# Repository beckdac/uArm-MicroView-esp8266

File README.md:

uArm-MicroView-esp8266
======================

uArm control PCB with MicroView (Arduino w/ OLED) and esp8266 WiFi/UART bridge

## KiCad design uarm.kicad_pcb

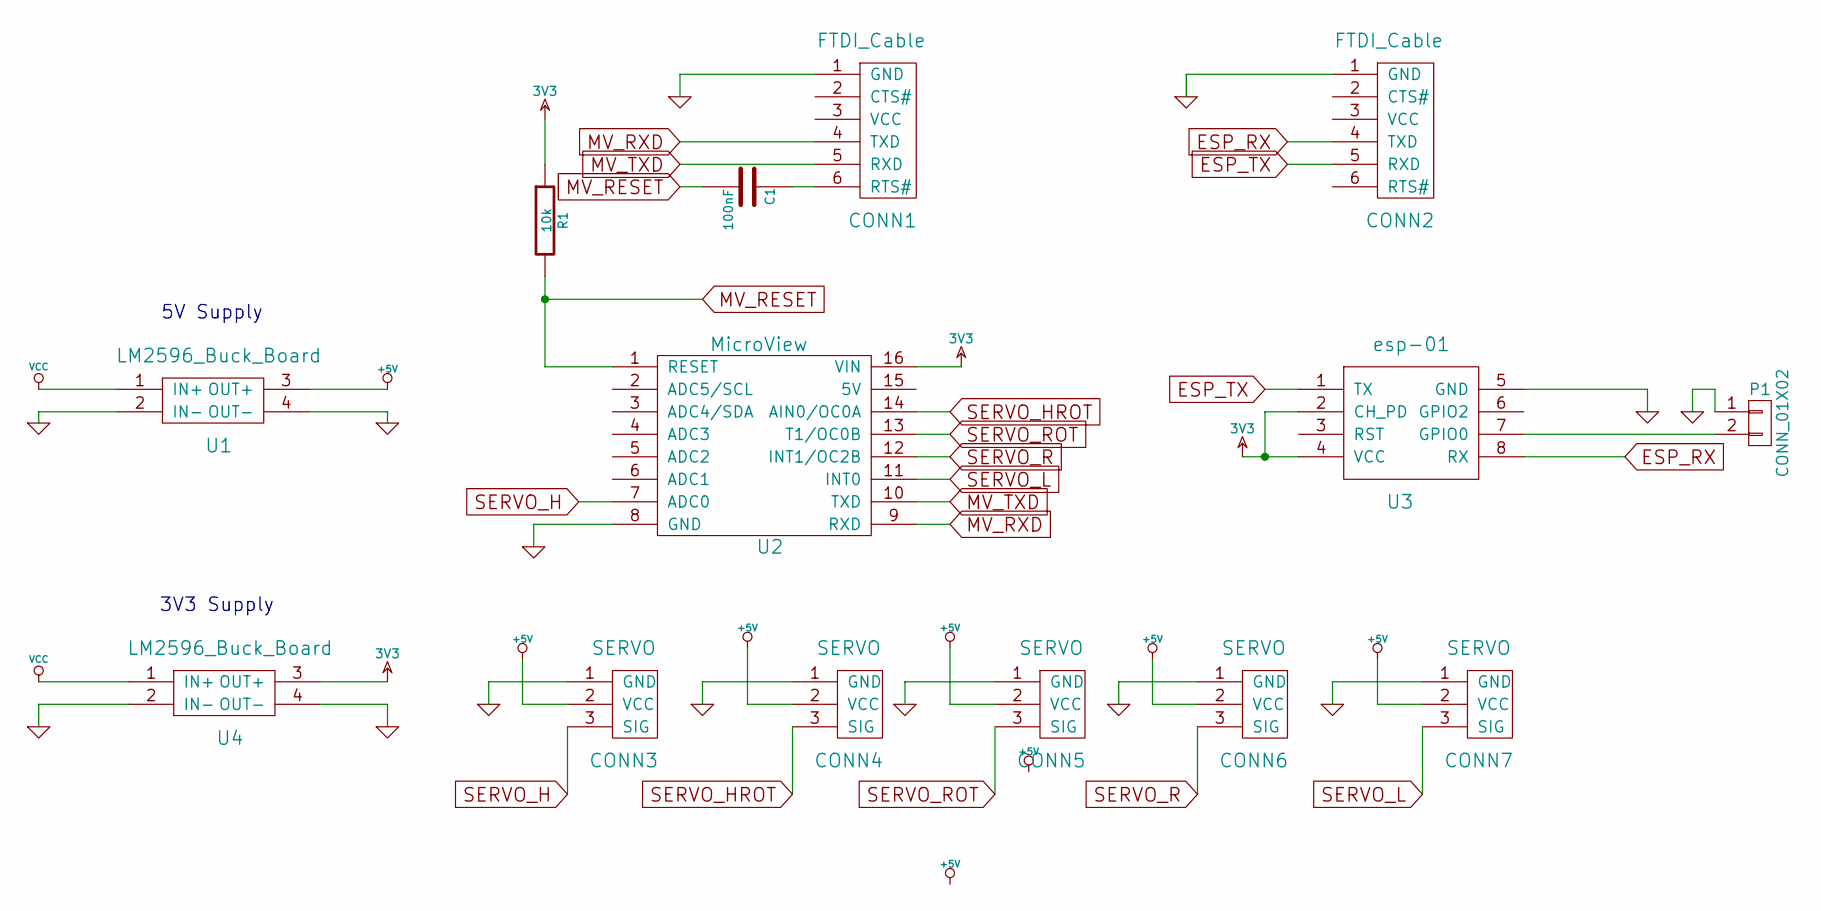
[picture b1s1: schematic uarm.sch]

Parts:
C1: 100nF; C1
CONN1, CONN2: FTDI_Cable; Pin_Header_Angled_1x06
CONN3, CONN4, CONN5, CONN6, CONN7: SERVO; Pin_Header_Straight_1x03
P1: CONN_01X02; Pin_Header_Straight_1x02
R1: 10k; R1
U1, U4: LM2596_Buck_Board; LM2596_BUCK_BOARD
U2: MicroView; MICROVIEW
U3: esp-01; ESP_01

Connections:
3V3: R1.1, U2.16 (VIN), U3.2 (CH_PD), U3.4 (VCC), U4.3 (OUT+)
+5V: CONN3.2 (VCC), CONN4.2 (VCC), CONN5.2 (VCC), CONN6.2 (VCC), CONN7.2 (VCC), U1.3 (OUT+)
ESP_RX: CONN2.4 (TXD), U3.8 (RX)
ESP_TX: CONN2.5 (RXD), U3.1 (TX)
GND: CONN1.1 (GND), CONN2.1 (GND), CONN3.1 (GND), CONN4.1 (GND), CONN5.1 (GND), CONN6.1 (GND), CONN7.1 (GND), P1.1, U1.2 (IN-), U1.4 (OUT-), U2.8 (GND), U3.5 (GND), U4.2 (IN-), U4.4 (OUT-)
MV_RESET: C1.2, R1.2, U2.1 (RESET)
MV_RXD: CONN1.4 (TXD), U2.9 (RXD)
MV_TXD: CONN1.5 (RXD), U2.10 (TXD)
unnamed: C1.1, CONN1.6 (RTS#)
unnamed: P1.2, U3.7 (GPIO0)
SERVO_H: CONN3.3 (SIG), U2.7 (ADC0)
SERVO_HROT: CONN4.3 (SIG), U2.14 (AIN0/OC0A)
SERVO_L: CONN7.3 (SIG), U2.11 (INT0)
SERVO_R: CONN6.3 (SIG), U2.12 (INT1/OC2B)
SERVO_ROT: CONN5.3 (SIG), U2.13 (T1/OC0B)
VCC: U1.1 (IN+), U4.1 (IN+)

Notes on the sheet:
5V Supply
3V3 Supply

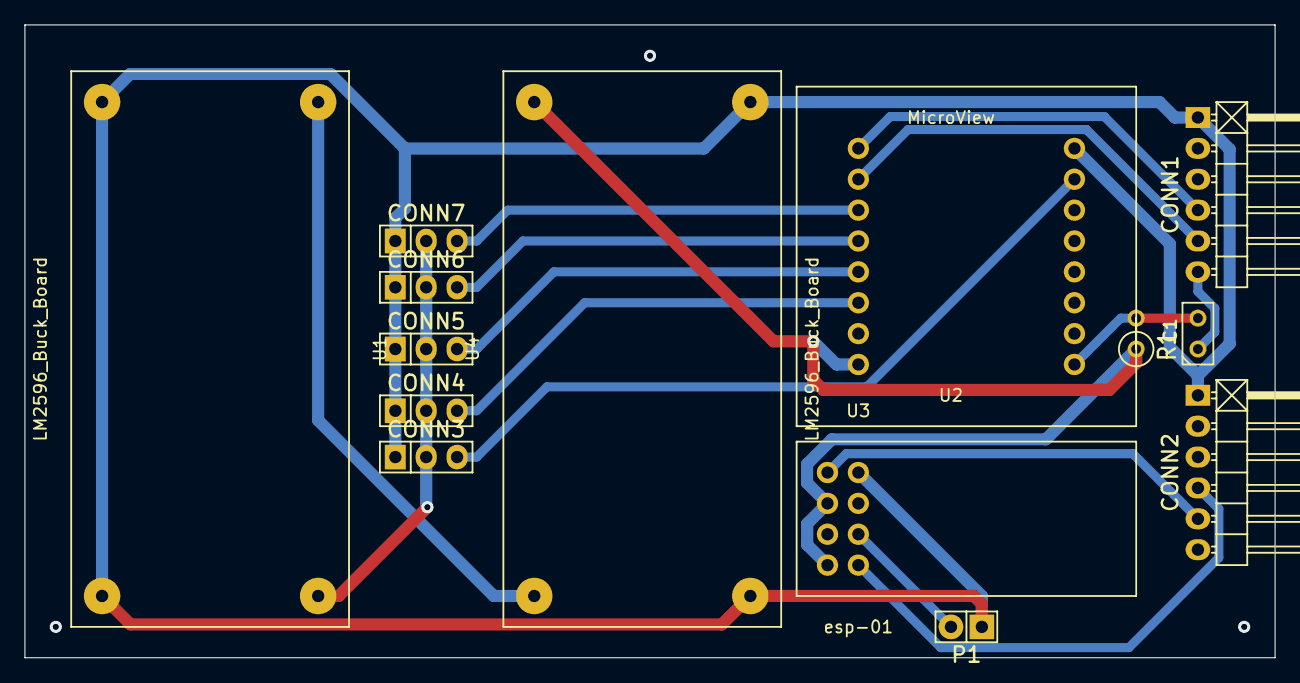
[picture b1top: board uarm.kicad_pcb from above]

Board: 2 copper layers, 102.9 x 52.1 mm, 14 parts (0 on the bottom side), 16 nets.

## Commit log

2014-12-04 initial import of design
2014-12-04 simplified routing
2014-12-08 first working prototype created
    dropped mutal reset pin handling from esp and microview; now esets
    have to occur in software or via a hard power down/up
    rotated LM2569 boards to simplify routing
    this design has been milled and soldered and works perfectly for
    programming both the microview and esp-01 with a FTDI ft232r 3v3
    cable.
2014-12-08 mounting box for electronics on arm
2014-12-09 updated width dimension to reflect reality
2014-12-17 added refined box parameters
